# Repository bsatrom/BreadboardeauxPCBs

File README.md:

# BreadboardeauxPCBs
PCB Design projects for Breadboardeaux Circuits and projects

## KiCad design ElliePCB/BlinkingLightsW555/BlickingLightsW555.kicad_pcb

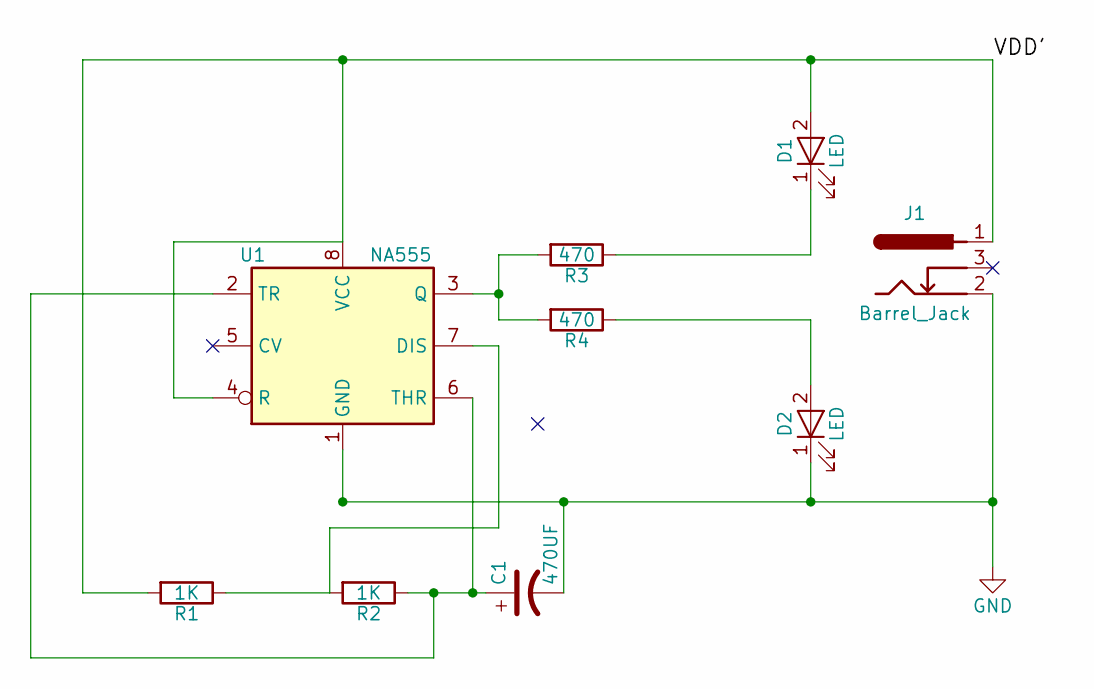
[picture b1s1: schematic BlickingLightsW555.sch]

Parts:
C1: 470UF; CP_Radial_D14.0mm_P5.00mm
D1, D2: LED; LED-10MM
J1: Barrel_Jack; CUI-PJ-102A_dc-barrel-jack-3-pad
R1, R2: 1K; R_Axial_DIN0411_L9.9mm_D3.6mm_P15.24mm_Horizontal
R3, R4: 470; R_Axial_DIN0411_L9.9mm_D3.6mm_P15.24mm_Horizontal
U1: NA555; DIP-8_W7.62mm_Socket_LongPads

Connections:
/VDD': D1.2 (A), J1.1, R1.2, U1.4 (R), U1.8 (VCC)
GND: C1.2, D2.1 (K), J1.2, U1.1 (GND)
unnamed: C1.1, R2.1, U1.2 (TR), U1.6 (THR)
unnamed: D1.1 (K), R3.1
unnamed: D2.2 (A), R4.1
unnamed: R1.1, R2.2, U1.7 (DIS)
unnamed: R3.2, R4.2, U1.3 (Q)

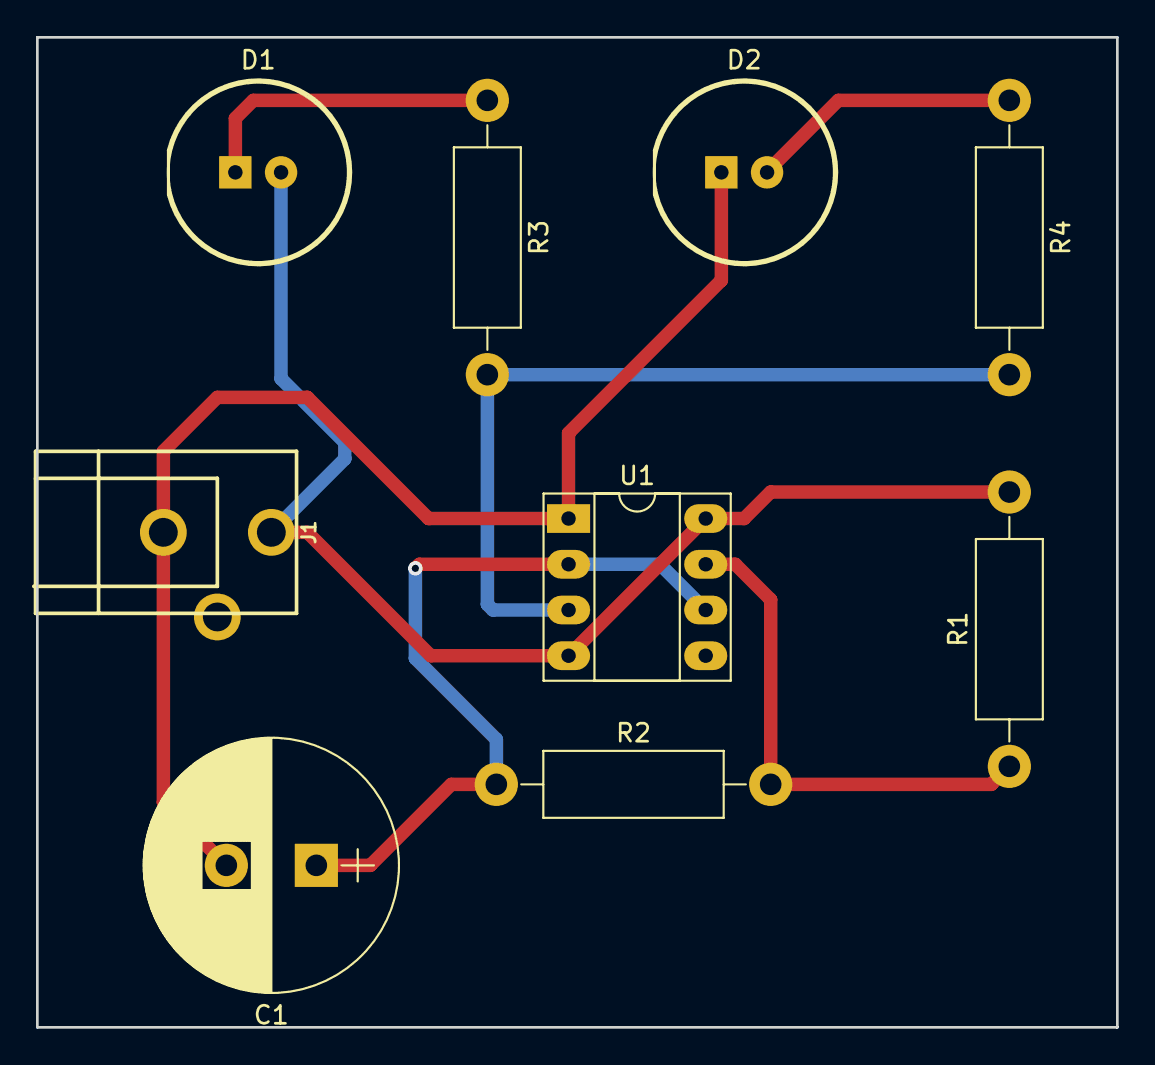
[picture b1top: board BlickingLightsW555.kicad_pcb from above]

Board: 2 copper layers, 60.0 x 55.0 mm, 9 parts (0 on the bottom side), 7 nets.

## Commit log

2018-02-23 added PCB design for Ellie Saves the Day
2018-04-13 added KiCad design files
